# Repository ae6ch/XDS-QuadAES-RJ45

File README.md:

# XDS-QuadAES-Studiohub
6/17/21 - First batch being made at JLCPCB for testing

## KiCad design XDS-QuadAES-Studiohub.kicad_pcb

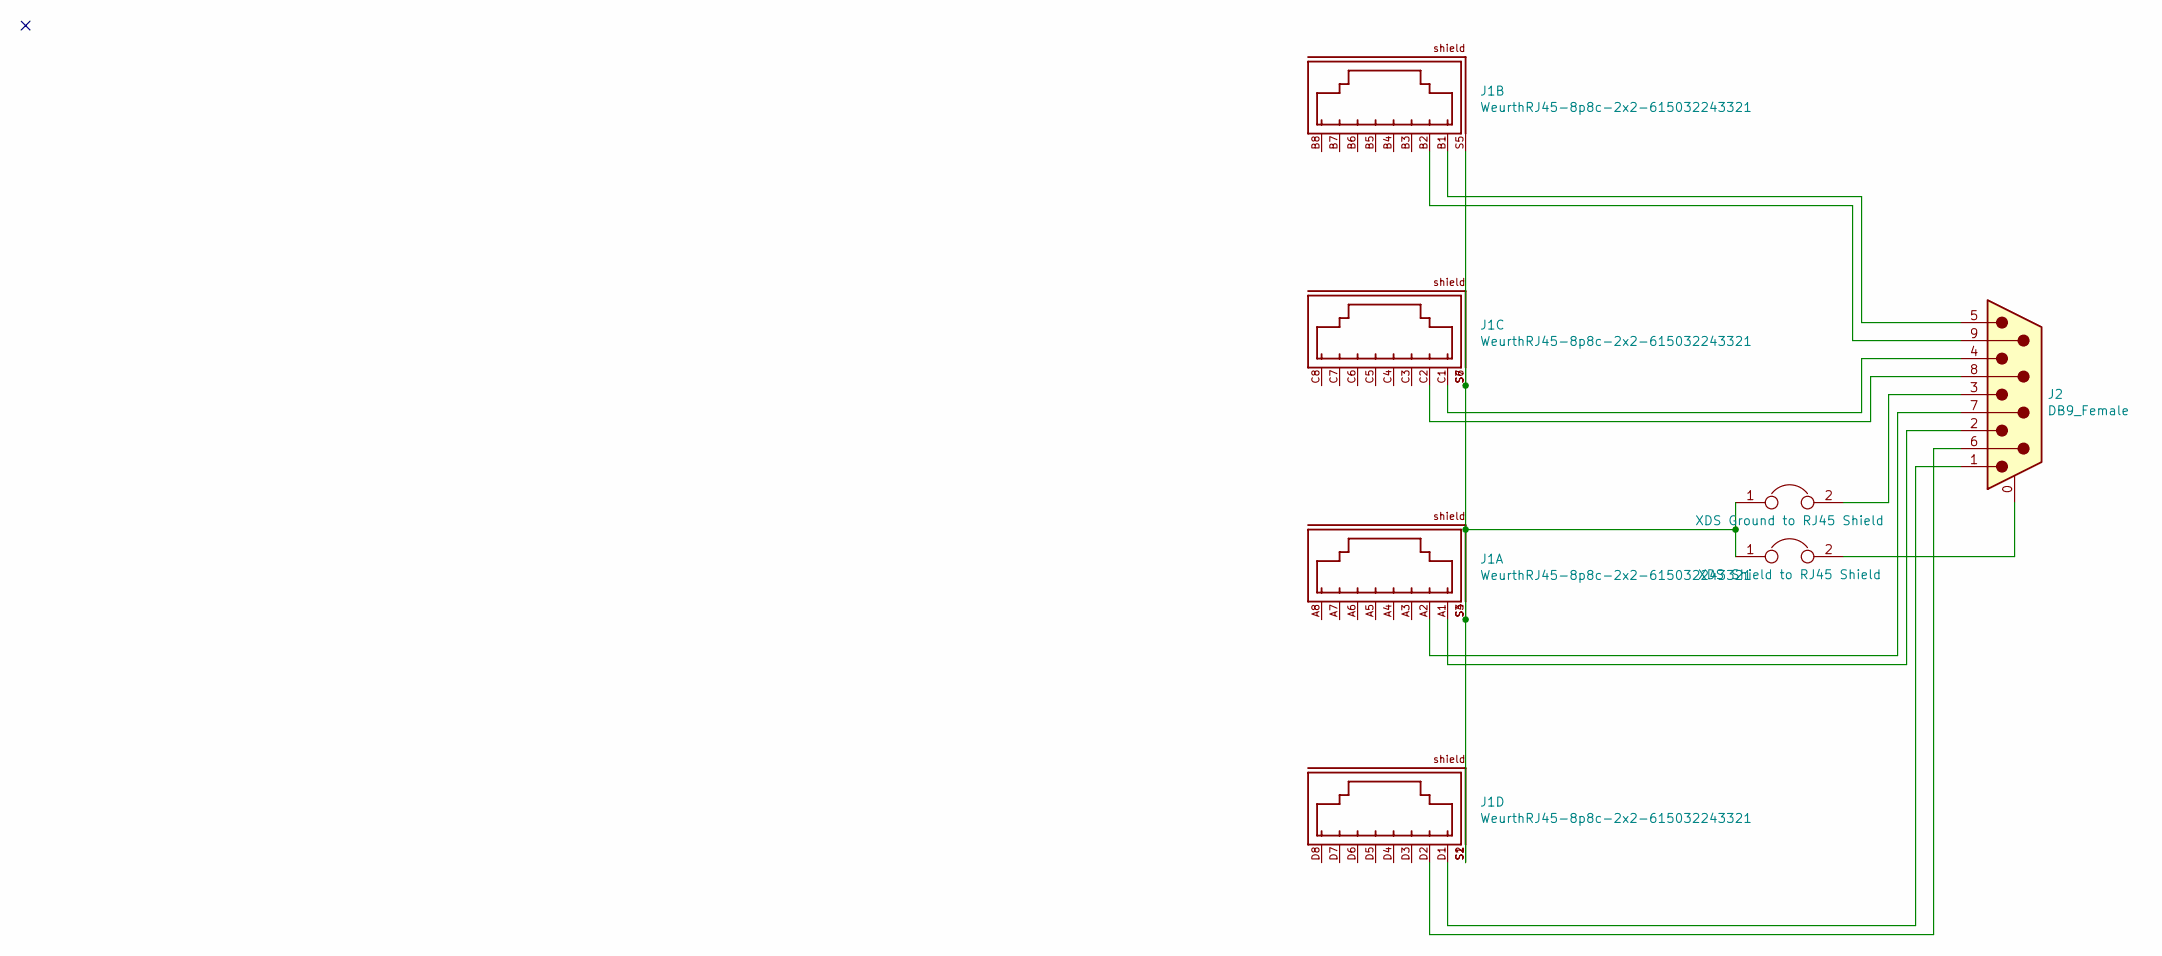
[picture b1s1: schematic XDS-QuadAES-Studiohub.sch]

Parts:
J1: WeurthRJ45-8p8c-2x2-615032243321; 615032243321; PART-NUMBER 615032243321
J2: DB9_Female; DSUB-9_Female_Horizontal_P2.77x2.84mm_EdgePinOffset7.70mm_H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
JP1: XDS Ground to RJ45 Shield; PinHeader_1x02_P2.54mm_Vertical
JP2: XDS Shield to RJ45 Shield; PinHeader_1x02_P2.54mm_Vertical

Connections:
unnamed: J1.A1, J2.2
unnamed: J1.A2, J2.7
unnamed: J1.B1, J2.5
unnamed: J1.B2, J2.9
unnamed: J1.C1, J2.4
unnamed: J1.C2, J2.8
unnamed: J1.D1, J2.1
unnamed: J1.D2, J2.6
unnamed: J1.S1, J1.S2, J1.S3, J1.S4, J1.S5, J1.S6, J1.S7, JP1.1, JP2.1
unnamed: J2.0 (PAD), JP2.2
unnamed: J2.3, JP1.2

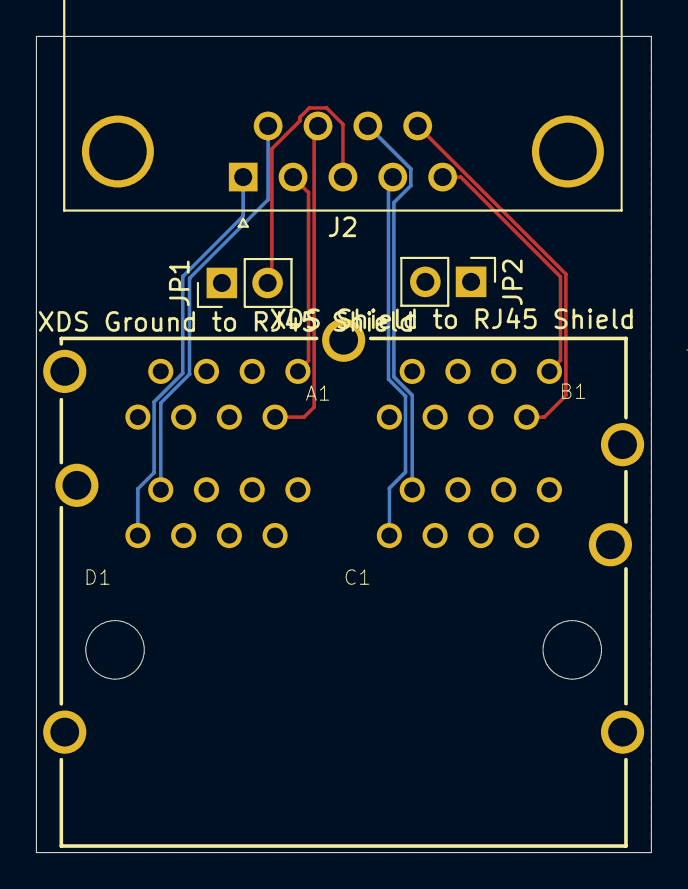
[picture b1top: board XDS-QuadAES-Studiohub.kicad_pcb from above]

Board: 2 copper layers, 34.2 x 45.3 mm, 4 parts (0 on the bottom side), 11 nets.

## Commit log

2021-06-17 edited readme
2021-06-17 added gitignore
2021-07-06 minor changes
